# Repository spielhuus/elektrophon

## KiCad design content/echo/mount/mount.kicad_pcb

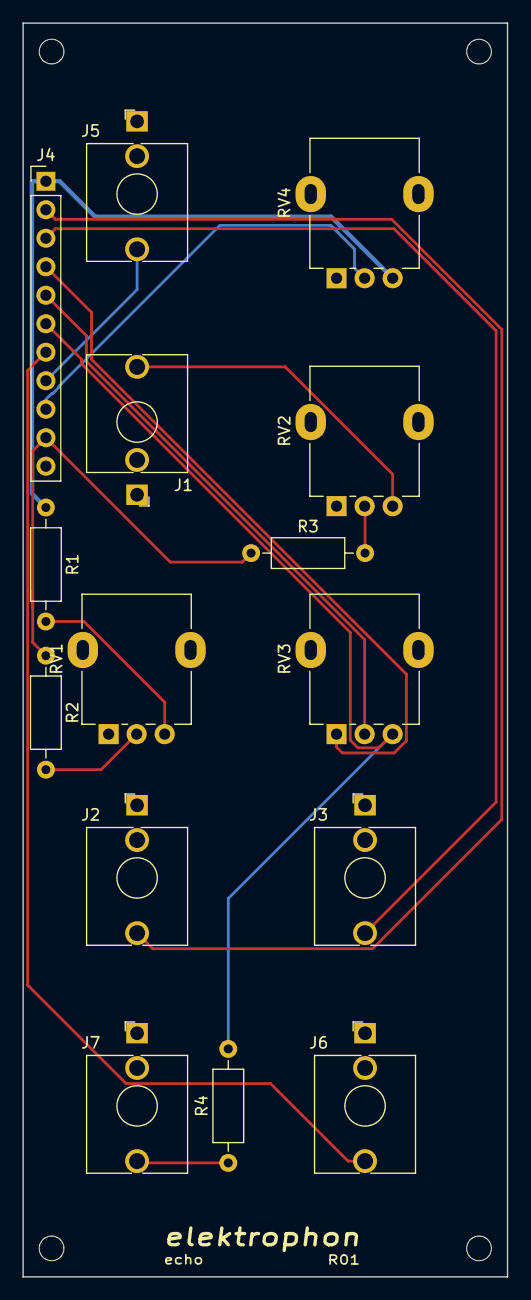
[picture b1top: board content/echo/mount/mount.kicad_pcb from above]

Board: 2 copper layers, 43.2 x 111.8 mm, 19 parts (0 on the bottom side), 16 nets.

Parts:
H1, H2, H3, H4: MountingHole; MountingHole_2.2mm_M2
J1: CV; Jack_3.5mm_WQP-PJ398SM_Vertical
J2, J3: IN; Jack_3.5mm_WQP-PJ398SM_Vertical
J4: Conn_01x11_Male; PinHeader_1x11_P2.54mm_Vertical
J5: RECIRC; Jack_3.5mm_WQP-PJ398SM_Vertical
J6: Mixed OUT; Jack_3.5mm_WQP-PJ398SM_Vertical
J7: delayed OUT; Jack_3.5mm_WQP-PJ398SM_Vertical
R1: 360; R_Axial_DIN0207_L6.3mm_D2.5mm_P10.16mm_Horizontal
R2: 300k; R_Axial_DIN0207_L6.3mm_D2.5mm_P10.16mm_Horizontal
R3: 100k; R_Axial_DIN0207_L6.3mm_D2.5mm_P10.16mm_Horizontal
R4: 1k; R_Axial_DIN0207_L6.3mm_D2.5mm_P10.16mm_Horizontal
RV1: 100k; Potentiometer_Alpha_RD901F-40-00D_Single_Vertical
RV2, RV4: 10k; Potentiometer_Alpha_RD901F-40-00D_Single_Vertical
RV3: 10k LIN; Potentiometer_Alpha_RD901F-40-00D_Single_Vertical

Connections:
+15V: J4.1, R1.1, RV4.3
/CV: J4.10, R2.1, R3.1
/IN1: J2.T, J4.2
/IN2: J3.T, J4.3
/MIXED_OUT: J4.7, J6.T
/MIX_1: J4.4, RV3.1
/MIX_2: J4.5, RV3.2
/MIX_3: J4.6, R4.2, RV3.3
/RECIRC_ATTEN: J4.9, RV4.2
/RECIRC_CV: J4.8, J5.T
GND: J1.S, J2.S, J3.S, J4.11, J5.S, J6.S, J7.S, RV1.1, RV2.1, RV4.1
unnamed: J1.T, RV2.3
unnamed: J7.T, R4.1
unnamed: R1.2, RV1.3
unnamed: R2.2, RV1.2
unnamed: R3.2, RV2.2

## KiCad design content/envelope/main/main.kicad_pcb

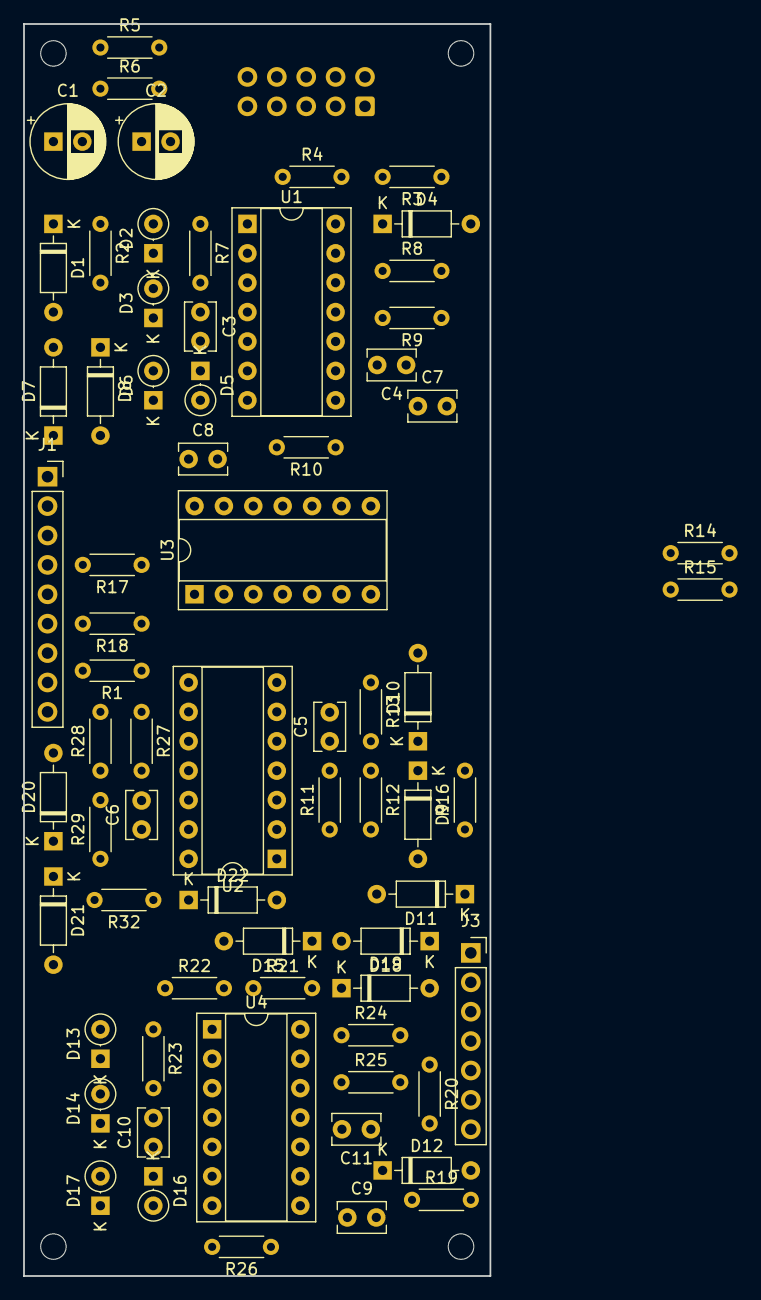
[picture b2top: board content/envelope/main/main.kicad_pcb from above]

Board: 2 copper layers, 40.3 x 108.2 mm, 74 parts (1 on the bottom side), 55 nets, no tracks yet.

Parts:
C1, C2: 22u; CP_Radial_D6.3mm_P2.50mm
C3, C4, C5, C6, C8, C10, C11: 0.1u; C_Rect_L4.0mm_W2.5mm_P2.50mm
C7, C9: 2.2u; C_Rect_L4.0mm_W2.5mm_P2.50mm
D1, D4, D7, D8, D9, D10, D11, D12, D15, D18, D19, D20, D21, D22: D; D_DO-35_SOD27_P7.62mm_Horizontal
D2, D3, D5, D6, D13, D14, D16, D17: D; D_DO-35_SOD27_P2.54mm_Vertical_KathodeUp
H1, H2, H3, H4: MountingHole; MountingHole_2.2mm_M2
J1: Conn_01x09_Female; PinSocket_1x09_P2.54mm_Vertical
J2: IDC Header; IDC-Header_2x05_P2.54mm_Vertical
J3: Conn_01x07_Female; PinSocket_1x07_P2.54mm_Vertical
R1, R16, R19, R32: 100k; R_Axial_DIN0204_L3.6mm_D1.6mm_P5.08mm_Horizontal
R2, R20: 27k; R_Axial_DIN0204_L3.6mm_D1.6mm_P5.08mm_Horizontal
R3, R21: 390k; R_Axial_DIN0204_L3.6mm_D1.6mm_P5.08mm_Horizontal
R4, R9, R22, R25: 47k; R_Axial_DIN0204_L3.6mm_D1.6mm_P5.08mm_Horizontal
R5, R6: 10; R_Axial_DIN0204_L3.6mm_D1.6mm_P5.08mm_Horizontal
R7, R23: 470k; R_Axial_DIN0204_L3.6mm_D1.6mm_P5.08mm_Horizontal
R8, R24: 2.2k; R_Axial_DIN0204_L3.6mm_D1.6mm_P5.08mm_Horizontal
R10, R26: 10k; R_Axial_DIN0204_L3.6mm_D1.6mm_P5.08mm_Horizontal
R11, R27: 36k; R_Axial_DIN0204_L3.6mm_D1.6mm_P5.08mm_Horizontal
R12, R14, R15, R17, R18, R28: 1k; R_Axial_DIN0204_L3.6mm_D1.6mm_P5.08mm_Horizontal
R13, R29: 220; R_Axial_DIN0204_L3.6mm_D1.6mm_P5.08mm_Horizontal
U1, U2, U4: LM324; DIP-14_W7.62mm_Socket
U3: 4001; DIP-14_W7.62mm_Socket

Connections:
+5V: J1.2, J2.9, J2.10
+15V: C1.1, C3.1, C5.1, C8.1, C10.1, R5.1, R11.2, R27.2, U1.4, U2.4, U3.14, U4.4
-15V: C2.2, C4.2, C6.2, C11.2, R6.1, U1.11, U2.11, U4.11
/sheet61728A8D/AA1: D7.1, J1.3
/sheet61728A8D/AA2: J1.4, R17.2
/sheet61728A8D/DA1: D8.2, J1.5
/sheet61728A8D/DA2: J1.6, R18.2
/sheet61728A8D/EOE1: J1.9, U3.3
/sheet61728A8D/IN1: D1.2, J1.7, R1.2
/sheet61728A8D/OUT1: J1.8, R10.1, U1.8, U1.9, U1.13, U2.3, U2.6
/sheet61729057/AB1: D18.1, J3.1
/sheet61729057/AB2: J3.2, R14.2
/sheet61729057/DB1: D19.2, J3.3
/sheet61729057/DB2: J3.4, R15.2
/sheet61729057/EOE2: J3.7, U3.4
/sheet61729057/IN2: D12.2, J3.5, R19.2
/sheet61729057/OUT2: J3.6, R26.1, U4.8, U4.9
GND: C1.2, C2.1, C3.2, C4.1, C5.2, C6.1, C7.2, C8.2, C9.2, C10.2, C11.1, D11.2, D22.2, J1.1, J2.5, J2.6, J2.7, J2.8, R1.1, R4.1, R9.1, R13.1, R19.1, R22.1, R25.1, R29.1, U1.2, U3.7, U3.8, U3.9, U3.12, U3.13, U4.2
unnamed: C7.1, R17.1, R18.1, U1.10
unnamed: C9.1, R14.1, R15.1, U4.10
unnamed: D1.1, R2.2
unnamed: D2.1, D3.2
unnamed: D2.2, R7.1, U1.1
unnamed: D3.1, R8.2, U1.5
unnamed: D4.1, U1.14
unnamed: D4.2, R3.1, R4.2
unnamed: D5.1, D6.2, R10.2, U1.6
unnamed: D5.2, D6.1, D7.2, D8.1, U1.7
unnamed: D9.2, U2.1
unnamed: D9.1, D10.1, R16.2
unnamed: D10.2, U2.7
unnamed: D11.1, R16.1, U3.2
unnamed: D12.1, R20.2
unnamed: D13.1, D14.2
unnamed: D13.2, R23.1, U4.1
unnamed: D14.1, R24.2, U4.5
unnamed: D15.1, U4.14
unnamed: D15.2, R21.1, R22.2
unnamed: D16.1, D17.2, R26.2, U4.6
unnamed: D16.2, D17.1, D18.2, D19.1, U4.7
unnamed: D20.1, D21.1, R32.2
unnamed: D20.2, U2.8
unnamed: D21.2, U2.14
unnamed: D22.1, R32.1, U3.6
unnamed: R2.1, R3.2, R7.2, U1.3
unnamed: R8.1, R9.2, U1.12, U3.1
unnamed: R11.1, R12.2, U2.2
unnamed: R12.1, R13.2, U2.5
unnamed: R20.1, R21.2, R23.2, U4.3
unnamed: R24.1, R25.2, U3.5, U4.12
unnamed: R27.1, R28.2, U2.9
unnamed: R28.1, R29.2, U2.12
unnamed: U2.10, U2.13, U4.13
VN: J2.1, J2.2, R6.2
VP: J2.3, J2.4, R5.2

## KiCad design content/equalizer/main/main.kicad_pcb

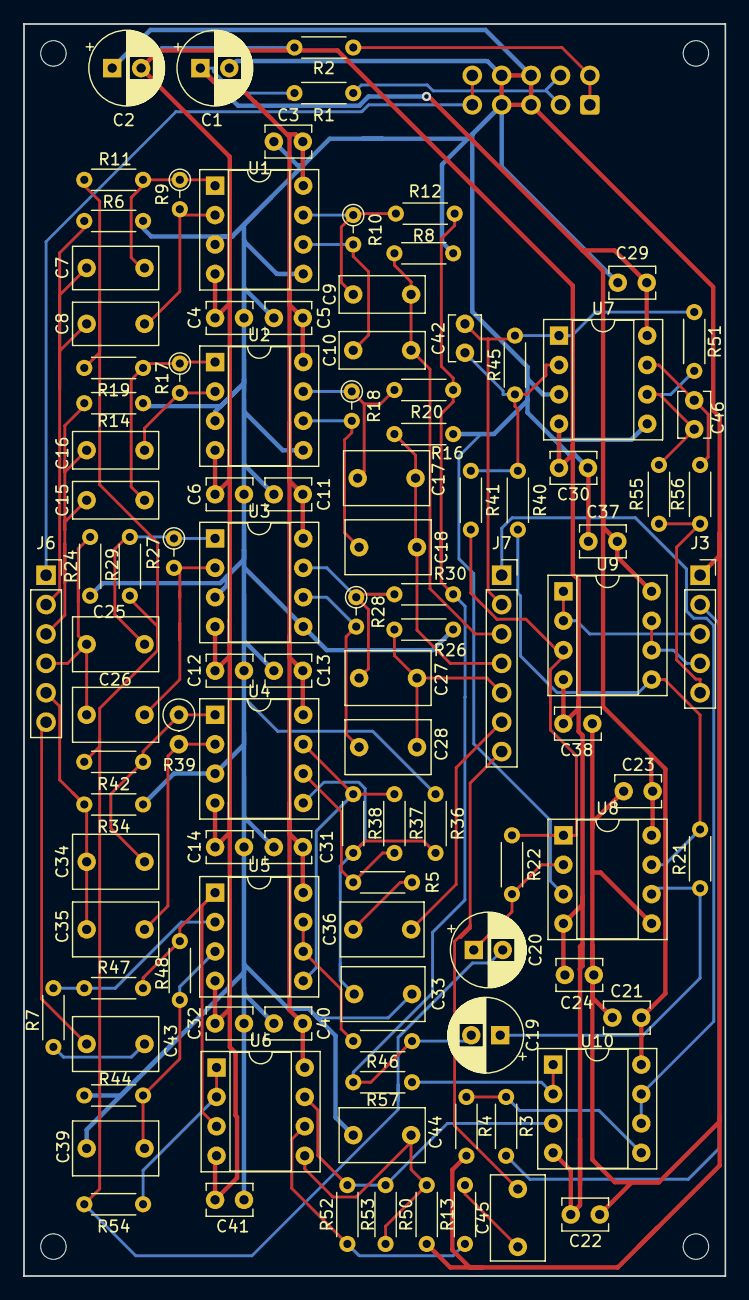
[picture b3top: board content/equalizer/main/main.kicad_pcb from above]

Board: 2 copper layers, 60.6 x 108.2 mm, 112 parts (1 on the bottom side), 61 nets.

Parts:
C1, C2: 22u; CP_Radial_D6.3mm_P2.50mm
C3, C4, C5, C6, C11, C12, C13, C14, C21, C22, C23, C24, C29, C30, C31, C32, C37, C38, C40, C41: 0.1u; C_Disc_D3.8mm_W2.6mm_P2.50mm
C7, C8: 47n; C_Rect_L7.2mm_W3.5mm_P5.00mm_FKS2_FKP2_MKS2_MKP2
C9, C10: 22n; C_Rect_L7.2mm_W3.0mm_P5.00mm_FKS2_FKP2_MKS2_MKP2
C15, C16: 10n; C_Rect_L7.2mm_W3.0mm_P5.00mm_FKS2_FKP2_MKS2_MKP2
C17, C18, C25, C26: 4n7; C_Rect_L7.2mm_W4.5mm_P5.00mm_FKS2_FKP2_MKS2_MKP2
C19, C20: 4u7; CP_Radial_D6.3mm_P2.50mm
C27, C28: 2n2; C_Rect_L7.2mm_W4.5mm_P5.00mm_FKS2_FKP2_MKS2_MKP2
C33, C36: 680p; C_Rect_L7.0mm_W4.5mm_P5.00mm
C34, C35: 1n; C_Rect_L7.2mm_W4.5mm_P5.00mm_FKS2_FKP2_MKS2_MKP2
C39, C43, C44, C45: 220p; C_Rect_L7.2mm_W4.5mm_P5.00mm_FKS2_FKP2_MKS2_MKP2
C42, C46: 47p; C_Disc_D3.8mm_W2.6mm_P2.50mm
H1, H2, H3, H4: MountingHole; MountingHole_2.2mm_M2
J1: IDC Header; IDC-Header_2x05_P2.54mm_Vertical
J3: Conn_01x05_Female; PinSocket_1x05_P2.54mm_Vertical
J6: Conn_01x06_Female; PinSocket_1x06_P2.54mm_Vertical
J7: Conn_01x07_Female; PinSocket_1x07_P2.54mm_Vertical
R1, R2: 10; R_Axial_DIN0204_L3.6mm_D1.6mm_P5.08mm_Horizontal
R3: 3k3; R_Axial_DIN0204_L3.6mm_D1.6mm_P5.08mm_Horizontal
R4: 470k; R_Axial_DIN0204_L3.6mm_D1.6mm_P5.08mm_Horizontal
R5, R36: 82k; R_Axial_DIN0204_L3.6mm_D1.6mm_P5.08mm_Horizontal
R6: 91k; R_Axial_DIN0204_L3.6mm_D1.6mm_P5.08mm_Horizontal
R7, R44: 130k; R_Axial_DIN0204_L3.6mm_D1.6mm_P5.08mm_Horizontal
R8: 30k; R_Axial_DIN0204_L3.6mm_D1.6mm_P5.08mm_Horizontal
R9, R27: 510k; R_Axial_DIN0204_L3.6mm_D1.6mm_P2.54mm_Vertical
R10: 680k; R_Axial_DIN0204_L3.6mm_D1.6mm_P2.54mm_Vertical
R11, R12, R19, R20, R21, R22, R29, R30, R40, R41, R42, R45: 47k; R_Axial_DIN0204_L3.6mm_D1.6mm_P5.08mm_Horizontal
R13, R50: 68k; R_Axial_DIN0204_L3.6mm_D1.6mm_P5.08mm_Horizontal
R14: 36k; R_Axial_DIN0204_L3.6mm_D1.6mm_P5.08mm_Horizontal
R16: 43k; R_Axial_DIN0204_L3.6mm_D1.6mm_P5.08mm_Horizontal
R17: 820k; R_Axial_DIN0204_L3.6mm_D1.6mm_P2.54mm_Vertical
R18: 910k; R_Axial_DIN0204_L3.6mm_D1.6mm_P2.54mm_Vertical
R24, R57: 22k; R_Axial_DIN0204_L3.6mm_D1.6mm_P5.08mm_Horizontal
R26: 24k; R_Axial_DIN0204_L3.6mm_D1.6mm_P5.08mm_Horizontal
R28: 560k; R_Axial_DIN0204_L3.6mm_D1.6mm_P2.54mm_Vertical
R34: 27k; R_Axial_DIN0204_L3.6mm_D1.6mm_P5.08mm_Horizontal
R37, R47: 16k5; R_Axial_DIN0204_L3.6mm_D1.6mm_P5.08mm_Horizontal
R38, R48, R53: 10k; R_Axial_DIN0204_L3.6mm_D1.6mm_P5.08mm_Horizontal
R39: 620k; R_Axial_DIN0207_L6.3mm_D2.5mm_P2.54mm_Vertical
R46, R54: 33k; R_Axial_DIN0204_L3.6mm_D1.6mm_P5.08mm_Horizontal
R51, R55: 4k7; R_Axial_DIN0204_L3.6mm_D1.6mm_P5.08mm_Horizontal
R52: 15k4; R_Axial_DIN0204_L3.6mm_D1.6mm_P5.08mm_Horizontal
R56: 330; R_Axial_DIN0204_L3.6mm_D1.6mm_P5.08mm_Horizontal
U1, U2, U3, U4, U5, U6, U7, U8, U9, U10: LF353; DIP-8_W7.62mm_Socket

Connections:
+5V: J1.9, J1.10, J6.1
+15V: C1.1, C3.2, C5.2, C11.2, C13.2, C21.2, C23.2, C29.2, C31.2, C37.2, C40.2, R1.1, U1.8, U2.8, U3.8, U4.8, U5.8, U6.8, U7.8, U8.8, U9.8, U10.8
-15V: C2.2, C4.1, C6.1, C12.1, C14.1, C22.1, C24.1, C30.1, C32.1, C38.1, C41.1, R2.1, U1.4, U2.4, U3.4, U4.4, U5.4, U6.4, U7.4, U8.4, U9.4, U10.4
A_B: C7.2, C8.2, J6.2, R6.2
B_B: C15.2, C16.2, J6.3, R14.2
COM_OUT_A: J3.4, U9.6, U9.7
COM_OUT_B: J3.3, U9.1, U9.2
C_B: C25.2, C26.2, J6.4, R24.2
D_B: C34.2, C35.2, J6.5, R34.2
E_B: C43.2, J6.6
F_A: J7.1, U10.6, U10.7
F_B: C9.2, C10.2, J7.3, R8.2
F_C: C42.1, J7.2, R45.1, R51.2, U7.1
GND: C1.2, C2.1, C3.1, C4.2, C5.1, C6.2, C11.1, C12.2, C13.1, C14.2, C21.1, C22.2, C23.1, C24.2, C29.1, C30.2, C31.1, C32.2, C33.1, C37.1, C38.2, C39.1, C40.1, C41.2, C44.1, J1.5, J1.6, J1.7, J1.8, J3.1, R4.2, R6.1, R8.1, R14.1, R16.1, R24.1, R26.1, R34.1, R36.1, R44.1, R50.1, U1.3, U1.5, U2.3, U2.5, U3.3, U3.5, U4.3, U7.3, U7.5, U8.3, U8.5
G_B: C17.2, C18.2, J7.4, R16.2
H_B: C27.2, C28.2, J7.5, R26.2
IN: J3.2, R3.2
I_B: C36.2, J7.6
J_B: C45.2, J7.7
unnamed: C7.1, R9.1, R11.1, U1.1
unnamed: C8.1, R9.2, U1.2
unnamed: C9.1, R10.1, R12.1, U1.7
unnamed: C10.1, R10.2, U1.6
unnamed: C15.1, R17.1, R19.1, U2.1
unnamed: C16.1, R17.2, U2.2
unnamed: C17.1, R18.1, R20.1, U2.7
unnamed: C18.1, R18.2, U2.6
unnamed: C19.1, R21.2, U8.6
unnamed: C19.2, R12.2, R20.2, R30.2, R46.2, R57.2
unnamed: C20.1, R22.2, U8.2
unnamed: C20.2, R11.2, R19.2, R29.2, R42.2, R54.2
unnamed: C25.1, R27.1, R29.1, U3.1
unnamed: C26.1, R27.2, U3.2
unnamed: C27.1, R28.1, R30.1, U3.7
unnamed: C28.1, R28.2, U3.6
unnamed: C33.2, R36.2, R38.2, U4.5
unnamed: C34.1, R39.1, R42.1, U4.1
unnamed: C35.1, R39.2, U4.2
unnamed: C36.1, R5.2
unnamed: C39.2, R44.2, R48.2, U5.3
unnamed: C42.2, R40.1, R41.1, R45.2, U7.2
unnamed: C43.1, R7.2
unnamed: C44.2, R50.2, R53.2, U6.5
unnamed: C45.1, R13.2
unnamed: C46.1, R56.2, U7.7
unnamed: C46.2, R51.1, R55.2, U7.6
unnamed: R3.1, R4.1, U10.5
unnamed: R13.1, R52.2, U6.6
unnamed: R21.1, R40.2, U8.7, U9.5
unnamed: R22.1, R41.2, U8.1, U9.3
unnamed: R37.1, R38.1, U4.7, U5.5
unnamed: R5.1, R37.2, U4.6
unnamed: R46.1, U5.6, U5.7
unnamed: R47.1, R48.1, U5.1, U6.3
unnamed: R7.1, R47.2, U5.2
unnamed: R52.1, R53.1, U6.7, U10.3
unnamed: R54.1, U6.1, U6.2
unnamed: R57.1, U10.1, U10.2
OUT: J3.5, R55.1, R56.1
VN: J1.1, J1.2, R2.2
VP: J1.3, J1.4, R1.2

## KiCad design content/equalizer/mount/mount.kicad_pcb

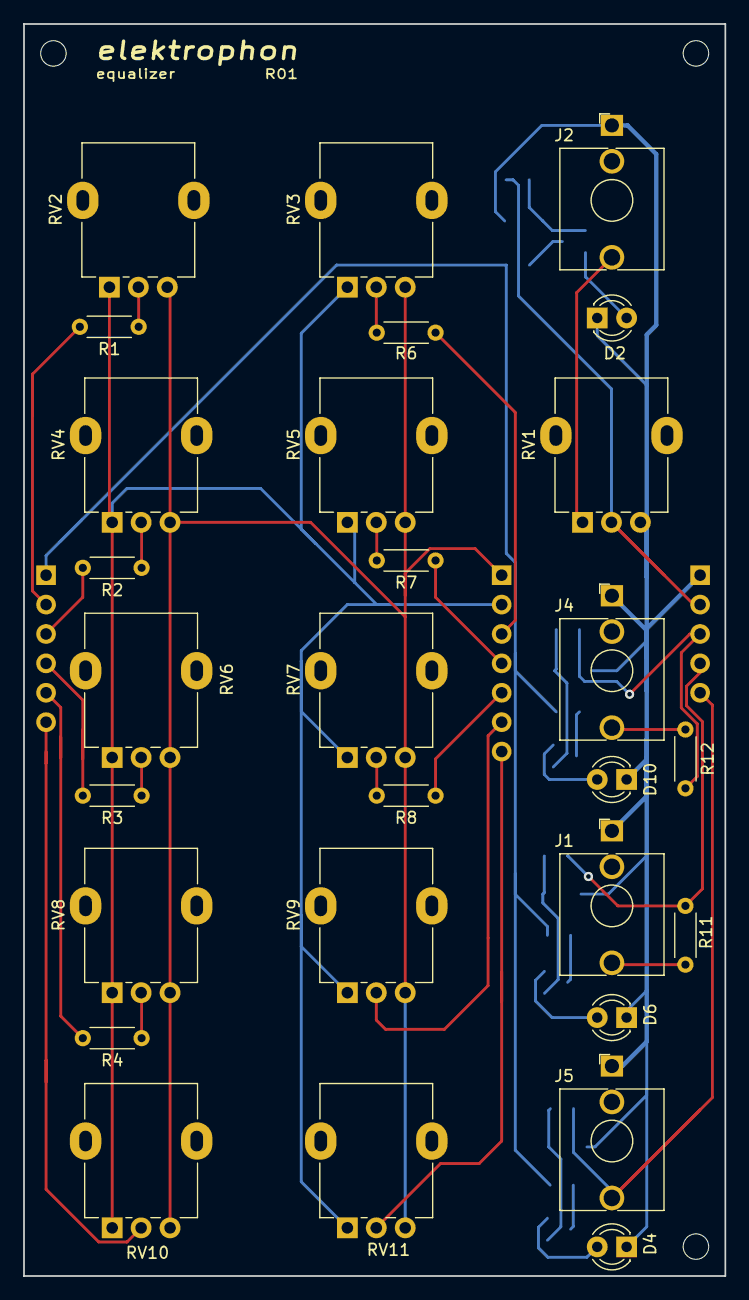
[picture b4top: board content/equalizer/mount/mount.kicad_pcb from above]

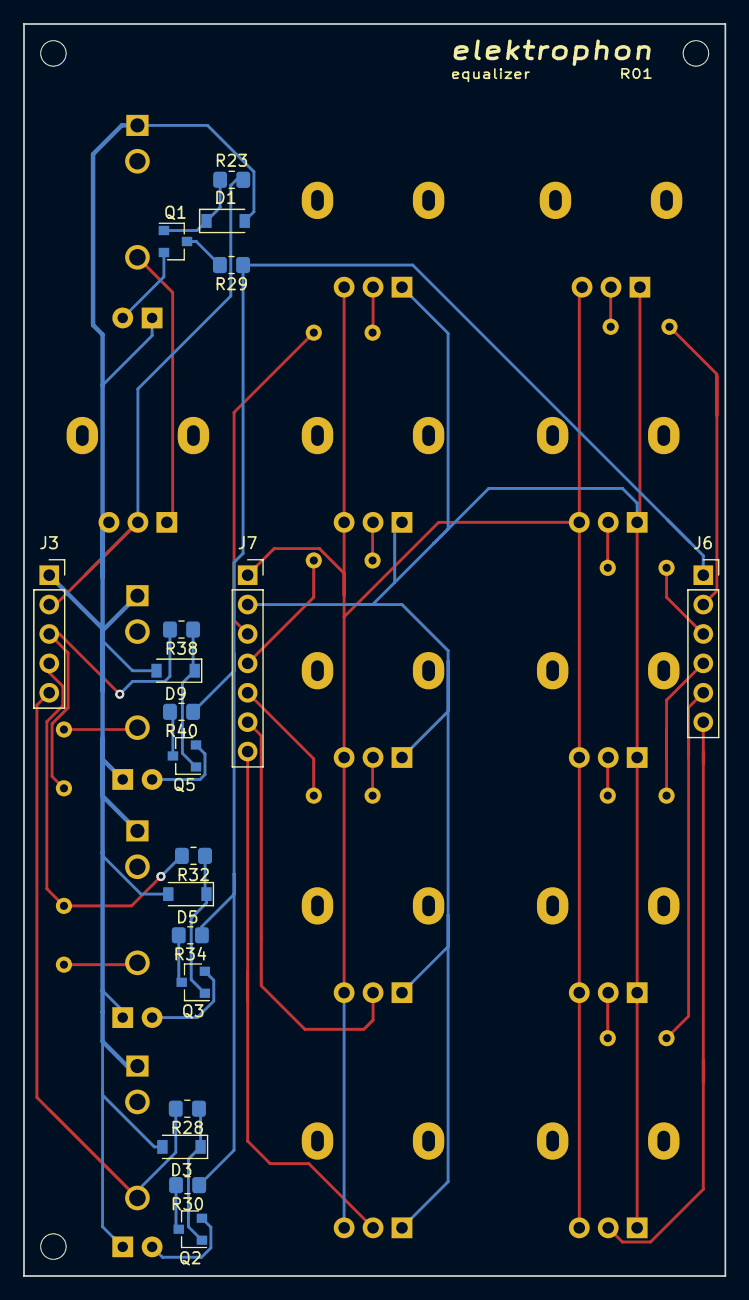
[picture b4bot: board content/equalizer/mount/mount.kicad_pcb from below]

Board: 2 copper layers, 60.6 x 108.2 mm, 50 parts (19 on the bottom side), 40 nets.

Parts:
D1, D3, D5, D9: 1N4148W; D_SOD-123
D2, D4, D6, D10: LED; LED_D3.0mm
H1, H2, H4: MountingHole; MountingHole_2.2mm_M2
J1, J2, J4, J5: AudioJack2_SwitchT; Jack_3.5mm_WQP-PJ398SM_Vertical
J3: Conn_01x05_Male; PinSocket_1x05_P2.54mm_Vertical
J6: Conn_01x06_Male; PinSocket_1x06_P2.54mm_Vertical
J7: Conn_01x07_Male; PinSocket_1x07_P2.54mm_Vertical
Q1, Q2, Q3, Q5: MMBT3904; SOT-23
R1: 39k; R_Axial_DIN0204_L3.6mm_D1.6mm_P5.08mm_Horizontal
R2: 62k; R_Axial_DIN0204_L3.6mm_D1.6mm_P5.08mm_Horizontal
R3: 36k; R_Axial_DIN0204_L3.6mm_D1.6mm_P5.08mm_Horizontal
R4: 47k; R_Axial_DIN0204_L3.6mm_D1.6mm_P5.08mm_Horizontal
R6: 51k; R_Axial_DIN0204_L3.6mm_D1.6mm_P5.08mm_Horizontal
R7: 68k; R_Axial_DIN0204_L3.6mm_D1.6mm_P5.08mm_Horizontal
R8: 43k; R_Axial_DIN0204_L3.6mm_D1.6mm_P5.08mm_Horizontal
R11, R12: 330; R_Axial_DIN0204_L3.6mm_D1.6mm_P5.08mm_Horizontal
R23, R28, R32, R38: 100k; R_0805_2012Metric_Pad1.20x1.40mm_HandSolder
R29, R34, R40: 5.1k; R_0805_2012Metric_Pad1.20x1.40mm_HandSolder
R30: 5k; R_0805_2012Metric_Pad1.20x1.40mm_HandSolder
RV1, RV2, RV3, RV4, RV5, RV6, RV7, RV8, RV9, RV10, RV11: 50k; Potentiometer_Alpha_RD901F-40-00D_Single_Vertical

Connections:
+5V: J6.1, R29.1, R30.1, R34.1, R40.1
A_B: J6.2, R1.2
B_B: J6.3, R2.2
COM_OUT_A: J3.4, R11.2, R32.2
COM_OUT_B: J3.3, R12.2, R38.2
C_B: J6.4, R3.2
D_B: J6.5, R4.2
E_B: J6.6, RV10.2
F_A: J7.1, RV2.3, RV3.3, RV4.3, RV5.3, RV6.3, RV7.3, RV8.3, RV9.3, RV10.3, RV11.3
F_B: J7.3, R6.2
F_C: J7.2, RV2.1, RV3.1, RV4.1, RV5.1, RV6.1, RV7.1, RV8.1, RV9.1, RV10.1, RV11.1
GND: D1.2, D2.1, D3.2, D4.1, D5.2, D6.1, D9.2, D10.1, J1.S, J2.S, J3.1, J4.S, J5.S, RV1.3
G_B: J7.4, R7.2
H_B: J7.5, R8.2
IN: J3.2, R23.2, RV1.2
I_B: J7.6, RV9.2
J_B: J7.7, RV11.2
unnamed: D1.1, Q1.1, R23.1
unnamed: D2.2, Q1.2
unnamed: D3.1, Q2.1, R28.1
unnamed: D4.2, Q2.2
unnamed: D5.1, Q3.1, R32.1
unnamed: D6.2, Q3.2
unnamed: D9.1, Q5.1, R38.1
unnamed: D10.2, Q5.2
unnamed: J1.T, R11.1
unnamed: J2.T, RV1.1
unnamed: J4.T, R12.1
unnamed: Q1.3, R29.2
unnamed: Q2.3, R30.2
unnamed: Q3.3, R34.2
unnamed: Q5.3, R40.2
unnamed: R1.1, RV2.2
unnamed: R2.1, RV4.2
unnamed: R3.1, RV6.2
unnamed: R4.1, RV8.2
unnamed: R6.1, RV3.2
unnamed: R7.1, RV5.2
unnamed: R8.1, RV7.2
OUT: J3.5, J5.T, R28.2

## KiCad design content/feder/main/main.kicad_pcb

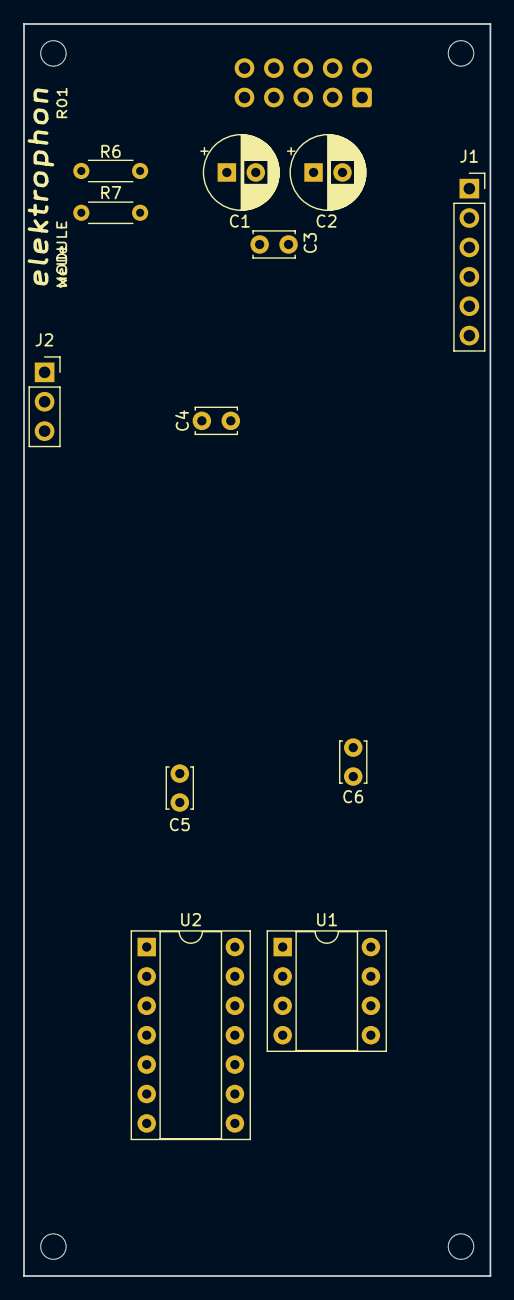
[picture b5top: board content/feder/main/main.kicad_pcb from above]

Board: 2 copper layers, 40.3 x 108.2 mm, 17 parts (1 on the bottom side), 6 nets, no tracks yet.

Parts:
C1, C2: 22u; CP_Radial_D6.3mm_P2.50mm
C3, C4, C5, C6: 0.1u; C_Disc_D3.4mm_W2.1mm_P2.50mm
H1, H2, H3, H4: MountingHole; MountingHole_2.2mm_M2
J1: 01x06 Female; PinSocket_1x06_P2.54mm_Vertical
J2: 01x03 Female; PinSocket_1x03_P2.54mm_Vertical
J4: 10 Pos; IDC-Header_2x05_P2.54mm_Vertical
R6, R7: 10; R_Axial_DIN0204_L3.6mm_D1.6mm_P5.08mm_Horizontal
U1: TL072; DIP-8_W7.62mm_Socket
U2: TL074; DIP-14_W7.62mm_Socket

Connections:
+5V: J1.1, J4.9, J4.10
+15V: C1.1, C3.1, C5.1, J1.5, R6.1, U1.8, U2.4
-15V: C2.2, C4.2, C6.2, R7.1, U1.4, U2.11
GND: C1.2, C2.1, C3.2, C4.1, C5.2, C6.1, J2.1, J4.5, J4.6, J4.7, J4.8
VN: J4.1, J4.2, R7.2
VP: J4.3, J4.4, R6.2

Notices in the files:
content/echo/mount/mount.kicad_pcb:
License CC BY 4.0 - Attribution 4.0 International
